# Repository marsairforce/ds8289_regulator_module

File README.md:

# A small voltage regulator on a board

This was designed around March 2017.

This is basically from their datasheet.

Using a switch mode buck converter IC, can use resistors to get different voltages output.  I built 2 kinds of this module, one for 5V and one for 12V. To control the voltage you just use different resistors to set up the voltage reference.

The datasheet sais this is rated up to 5A.

Total BOM including the printed circuit board is perhaps $20.

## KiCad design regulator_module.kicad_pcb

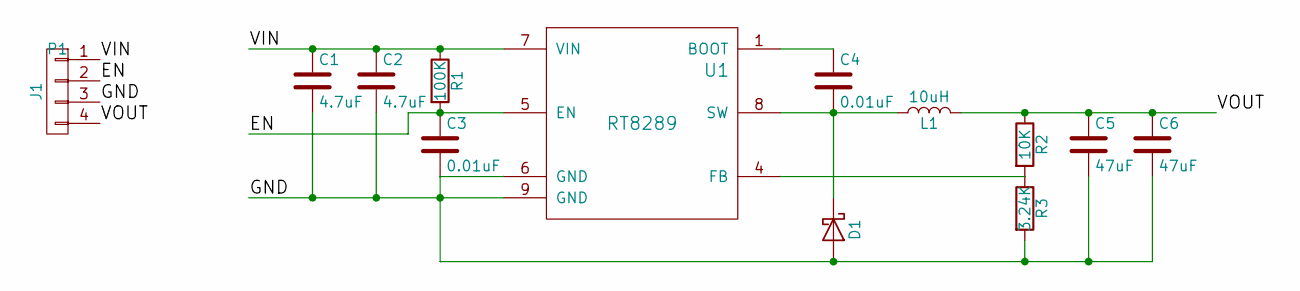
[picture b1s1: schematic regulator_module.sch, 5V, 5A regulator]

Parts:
C1, C2: 4.7uF; C_1206
C3, C4: 0.01uF; C_0603
C5, C6: 47uF; C_1206
D1: B550C-13-F; DO-214AB
L1: 10uH; Inductor_SMD_12.7mm
P1: J1; TerminalBlock_Pheonix_MPT-2.54mm_4pol
R1: 100K; R_1206
R2: 10K; R_1206
R3: 3.24K; R_1206
U1: RT8289; SOP-8_Exposed_Pad

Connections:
/EN: C3.1, P1.2, R1.2, U1.5 (EN)
/GND: C1.2, C2.2, C3.2, C5.2, C6.2, D1.2 (A), P1.3, R3.2, U1.6 (GND), U1.9 (GND)
/VIN: C1.1, C2.1, P1.1, R1.1, U1.7 (VIN)
/VOUT: C5.1, C6.1, L1.2, P1.4, R2.1
unnamed: C4.1, U1.1 (BOOT)
unnamed: C4.2, D1.1 (K), L1.1, U1.8 (SW)
unnamed: R2.2, R3.1, U1.4 (FB)

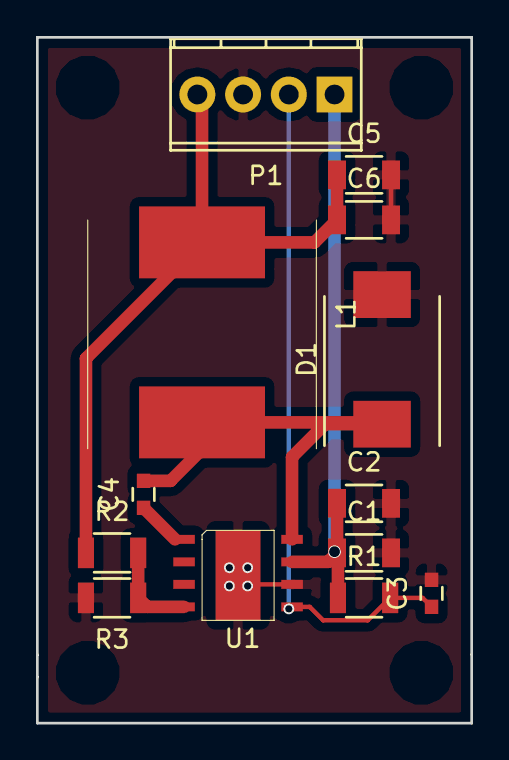
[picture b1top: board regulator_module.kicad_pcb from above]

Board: 2 copper layers, 24.1 x 38.1 mm, 13 parts (0 on the bottom side), 7 nets.

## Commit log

2018-04-15 add some documentation
    picture and the datasheet
